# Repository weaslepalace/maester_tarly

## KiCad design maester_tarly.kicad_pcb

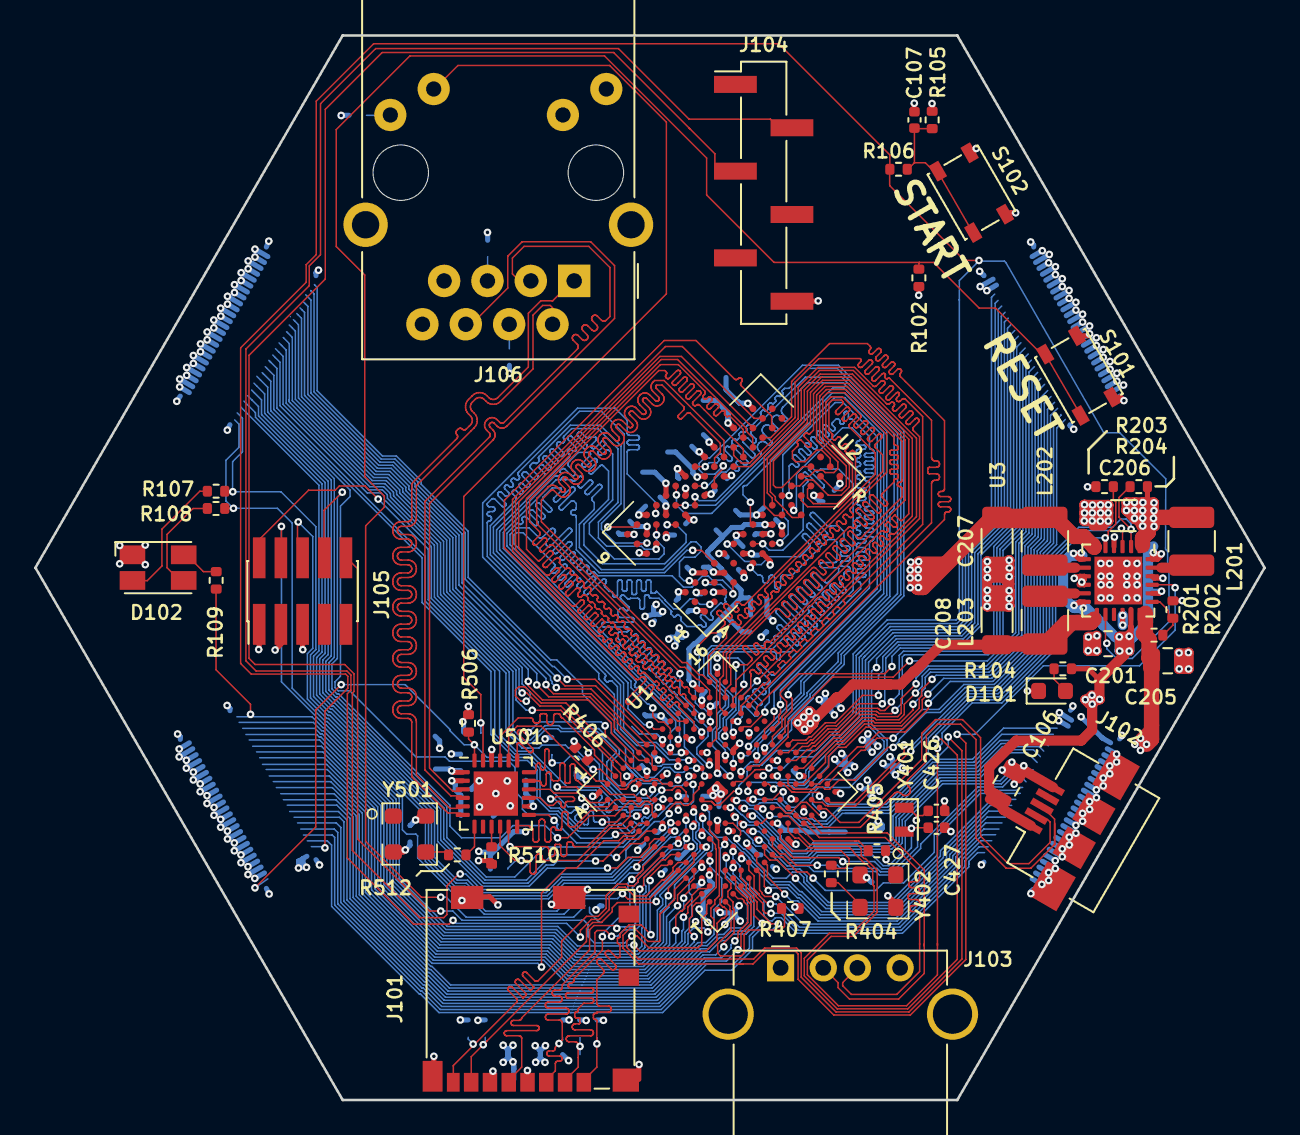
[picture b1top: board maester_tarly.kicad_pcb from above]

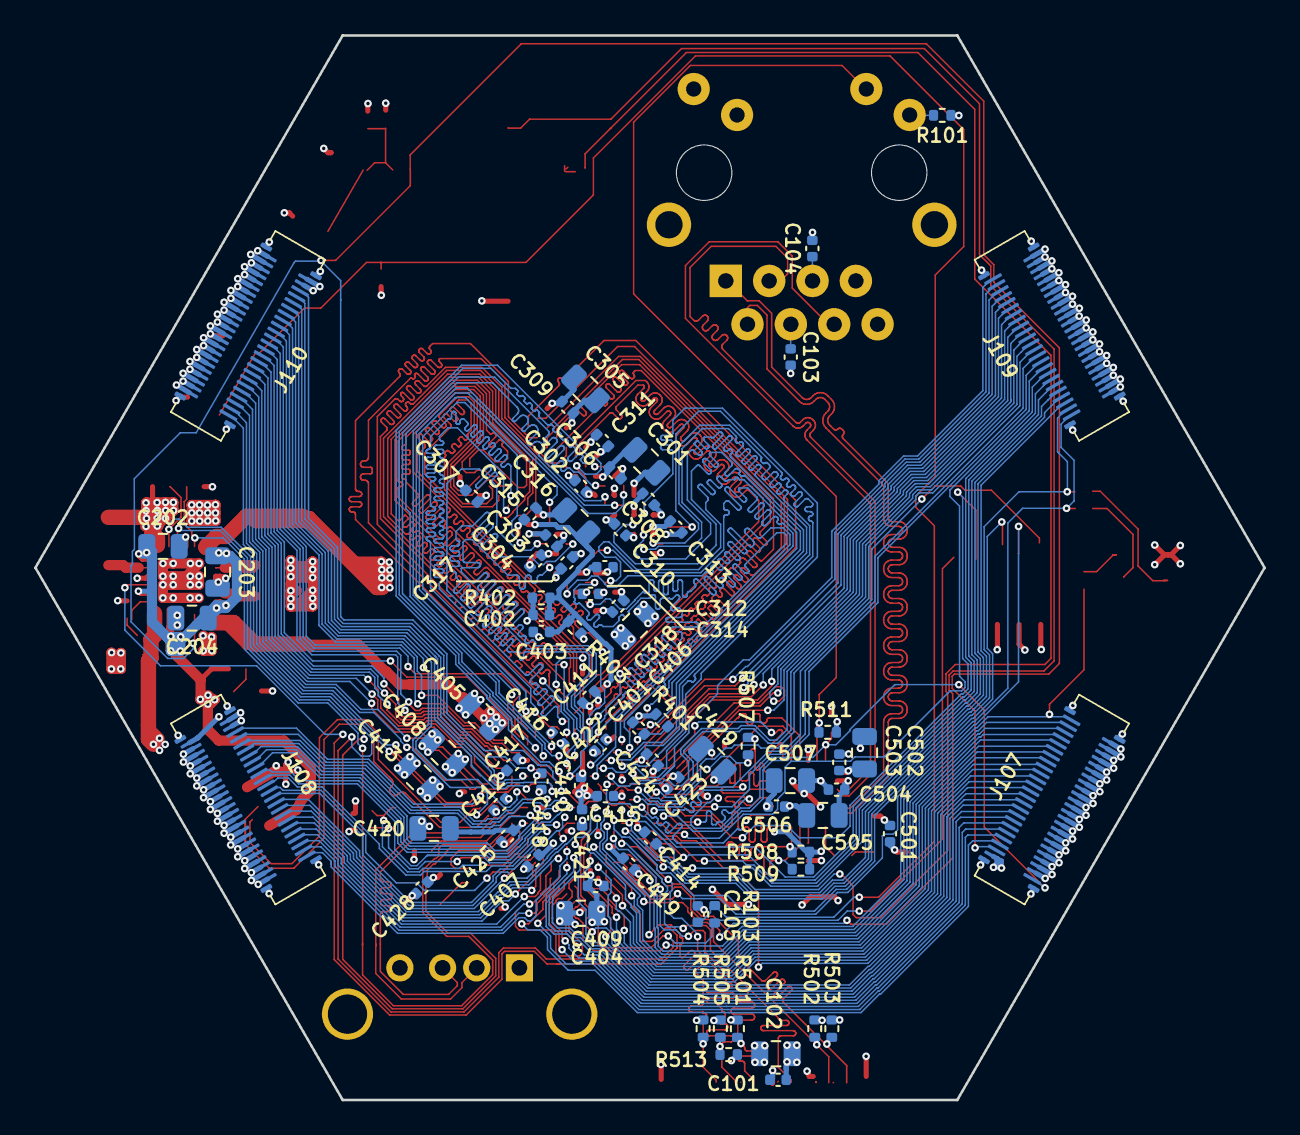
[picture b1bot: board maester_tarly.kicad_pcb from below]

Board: 4 copper layers, 72.0 x 62.4 mm, 126 parts (79 on the bottom side), 206 nets.

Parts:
C101, C103, C104, C105, C107, C302, C303, C304, C306, C307, C308, C309, C310, C311, C312, C313, C314, C315, C402, C403, C407, C409, C410, C411, C412, C414, C415, C416, C417, C418, C419, C421, C422, C423, C424, C425, C428, C501, C503, C504, C506: 100nF; C_0402_1005Metric
C102, C202, C203, C204, C205, C301, C305, C404, C405, C406, C408, C413, C420: 4.7uF; C_0805_2012Metric
C106: 10uF; C_0805_2012Metric
C201: 2.2uF; R_0805_2012Metric
C206, C207, C208: 22uF; R_1206_3216Metric
C316: 10nF; C_0805_2012Metric
C317, C318: 1nF; C_0402_1005Metric
C401: 22pF; C_0402_1005Metric
C426, C427: 20pF; C_0402_1005Metric
C429: 1uF; C_0805_2012Metric
C502, C505, C507: 2.2uF; C_0805_2012Metric
D101: Green; LED_0603_1608Metric
D102: ASMB-MTB0-0A3A2; LED_Avago_PLCC4_3.2x2.8mm_CW
J101: Micro_SD_Card_Det; microSD_HC_Molex_104031-0811
J102: USB_B_Micro; USB_Micro-B_Amphenol_10104110_Horizontal
J103: USB_A; USB_A_Stewart_SS-52100-001_Horizontal
J104: Conn_01x06; PinHeader_1x06_P2.54mm_Vertical_SMD_Pin1Left
J105: Conn_01x10; PinHeader_2x05_P1.27mm_Vertical_SMD
J106: RJ45_Amphenol_RJMG1BD3B8K1ANR
J107, J108, J109, J110: DF40GB(1.5)-48DS-0.4V; DF40GB(1.5)-48DS-0.4V(51)-CONNECTOR
L201, L202, L203: 2.2uH; L_1210_3225Metric
R101: 470R; R_0402_1005Metric
R102, R105, R203, R204, R407: 100k; R_0402_1005Metric
R103, R106: 100R; R_0402_1005Metric
R104, R107, R108, R109: 1k; R_0402_1005Metric
R201, R202: TBD; R_0402_1005Metric
R401: 20k; R_0402_1005Metric
R402, R403, R507: 4.7k; R_0402_1005Metric
R404, R510: 51R; R_0402_1005Metric
R405: 5.62k; R_0402_1005Metric
R406: 10R; R_0402_1005Metric
R501, R502, R503, R504, R505, R506, R508, R509, R511: 10k; R_0402_1005Metric
R512: 6.49k; R_0402_1005Metric
R513: 270k; R_0402_1005Metric
S101, S102: SW_Push; SW_SPST_PTS810
U1: SAM9X60; TFBGA228-SAM9X60
U2: W971GG6SB-18; WBGA84-DDR2-SDRAM
U3: MCP16501; QFN-24-1EP_4x4mm_P0.5mm_EP2.8x2.8mm
U501: KSZ8081RNA; QFN-24-1EP_4x4mm_P0.5mm_EP2.6x2.6mm
Y401: 32.768kHz; Crystal_SMD_2012-2Pin_2.0x1.2mm
Y402, Y501: DSC1001; VDFN4-3.2x2.5-DSC1001

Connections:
+1.8V: C207.1, C301.1, C302.1, C303.1, C304.1, C305.1, C306.1, C307.1, C308.1, C309.1, C310.1, C311.1, C312.1, C313.1, C314.1, C315.1, C317.1, C318.1, C402.1, C406.1, C411.1, C416.1, C422.1, L202.2, R402.1, U1.C10, U1.C13, U1.G14, U2.A1, U2.A9, U2.C1, U2.C3, U2.C7, U2.C9, U2.E1, U2.E9, U2.G1, U2.G3, U2.G7, U2.G9, U2.J1, U2.J9, U2.M9, U2.R1, U3.6
+1.15V: C208.1, C405.1, C410.1, C415.1, C421.1, L203.2, U1.F6, U1.F11, U1.L6, U3.13
+3V3: C101.1, C102.1, C206.1, C404.1, C407.1, C408.1, C409.1, C412.1, C413.1, C414.1, C417.1, C418.1, C419.1, C423.1, C424.1, C428.1, C501.1, C504.1, C505.1, C506.1, C507.1, D102.1, J101.4, J105.1, J108.1, J108.2, J108.4, L201.2, R101.1, R102.1, R105.1, R203.1, R204.2, R406.1, R501.1, R502.1, R503.1, R504.1, R505.1, R506.1, R507.1, R508.1, R509.1, R511.1, U1.C4, U1.C7, U1.G3, U1.K3, U1.K14, U1.L11, U1.N3, U1.P7, U1.P13, U3.1, U501.2, U501.14, Y402.4, Y501.4
+5V: C106.1, C201.1, C202.1, C203.1, C204.1, J102.1, J103.1, J110.2, J110.4, R104.1, U3.7, U3.12, U3.17, U3.20, U3.24
/CPU_CORE/CPU_DDR_CAS: U1.C12, U2.L7
/CPU_CORE/CPU_DDR_CKE: U1.F13, U2.K2
/CPU_CORE/CPU_DDR_CLK_N: U1.B14, U2.K8
/CPU_CORE/CPU_DDR_CLK_P: U1.A15, U2.J8
/CPU_CORE/CPU_DDR_CS: U1.E16, U2.L8
/CPU_CORE/CPU_DDR_HIGH_MASK: U1.C8, U2.B3
/CPU_CORE/CPU_DDR_HIGH_STROBE_N: U1.E9, U2.A8
/CPU_CORE/CPU_DDR_HIGH_STROBE_P: U1.D9, U2.B7
/CPU_CORE/CPU_DDR_LOW_MASK: U1.G11, U2.F3
/CPU_CORE/CPU_DDR_LOW_STROBE_N: U1.H13, U2.E8
/CPU_CORE/CPU_DDR_LOW_STROBE_P: U1.H12, U2.F7
/CPU_CORE/CPU_DDR_RAS: U1.E15, U2.K7
/CPU_CORE/CPU_DDR_VREF: C316.1, C402.2, C403.1, R402.2, R403.1, U1.A14, U2.J2
/CPU_CORE/CPU_DDR_WE: U1.D16, U2.K3
/CPU_CORE/CPU_JTAG_TCK: J105.4, U1.R3
/CPU_CORE/CPU_JTAG_TDI: J105.8, U1.F3
/CPU_CORE/CPU_JTAG_TDO: J105.6, U1.H5
/CPU_CORE/CPU_JTAG_TMS: J105.2, U1.F5
/CPU_CORE/CPU_SHUTDOWN: U1.R11, U3.3
/CPU_CORE/CPU_USB_DEVICE_N: J103.2, U1.R12
/CPU_CORE/CPU_USB_DEVICE_P: J103.3, U1.T12
/CPU_CORE/CPU_USB_HOST_N: J102.2, U1.T14
/CPU_CORE/CPU_USB_HOST_P: J102.3, U1.T13
/CPU_CORE/CPU_WAKEUP: R203.2, U1.T11, U3.5
/CPU_CORE/addr0: U1.A13, U2.M8
/CPU_CORE/addr1: U1.D15, U2.M3
/CPU_CORE/addr2: U1.B12, U2.M7
/CPU_CORE/addr3: U1.E11, U2.N2
/CPU_CORE/addr4: U1.A12, U2.N8
/CPU_CORE/addr5: U1.B16, U2.N3
/CPU_CORE/addr6: U1.F16, U2.N7
/CPU_CORE/addr7: U1.D14, U2.P2
/CPU_CORE/addr8: U1.C11, U2.P8
/CPU_CORE/addr9: U1.E13, U2.P3
/CPU_CORE/addr10: U1.D12, U2.M2
/CPU_CORE/addr11: U1.B11, U2.P7
/CPU_CORE/addr12: U1.C15, U2.R2
/CPU_CORE/bank0: U1.E14, U2.L2
/CPU_CORE/bank1: U1.F14, U2.L3
/CPU_CORE/bank2: U1.C16, U2.L1
/CPU_CORE/data0: U1.J13, U2.G8
/CPU_CORE/data1: U1.H11, U2.G2
/CPU_CORE/data2: U1.J11, U2.H7
/CPU_CORE/data3: U1.H16, U2.H3
/CPU_CORE/data4: U1.H15, U2.H1
/CPU_CORE/data5: U1.J14, U2.H9
/CPU_CORE/data6: U1.H10, U2.F1
/CPU_CORE/data7: U1.J16, U2.F9
/CPU_CORE/data8: U1.A9, U2.C8
/CPU_CORE/data9: U1.F10, U2.C2
/CPU_CORE/data10: U1.B9, U2.D7
/CPU_CORE/data11: U1.C9, U2.D3
/CPU_CORE/data12: U1.G9, U2.D1
/CPU_CORE/data13: U1.F9, U2.D9
/CPU_CORE/data14: U1.D11, U2.B1
/CPU_CORE/data15: U1.D8, U2.B9
/CPU_IO/CPU_DBG_UART_RX: J104.3, U1.G8
/CPU_IO/CPU_DBG_UART_TX: J104.2, U1.L2
/CPU_IO/CPU_ETH_LED: J106.L2, R511.2, U501.23
/CPU_IO/CPU_ETH_RX_N: J106.R6, U501.3
/CPU_IO/CPU_ETH_RX_P: J106.R3, U501.4
/CPU_IO/CPU_ETH_TX_N: J106.R2, U501.5
/CPU_IO/CPU_ETH_TX_P: J106.R1, U501.6
/CPU_IO/CPU_MMC_CLK: J101.5, U1.J3
/CPU_IO/CPU_MMC_CMD: J101.3, R501.2, U1.K2
/CPU_IO/PHY_CLK: U1.E3, U501.16
/CPU_IO/PHY_IRQ: R507.2, U1.E6, U501.18
/CPU_IO/PHY_MDC: R508.2, U1.D2, U501.11
/CPU_IO/PHY_MDIO: R509.2, U1.E1, U501.10
/CPU_IO/PHY_RXD0: U1.F4, U501.13
/CPU_IO/PHY_RXD1: U1.C1, U501.12
/CPU_IO/PHY_RXDV: U1.D1, U501.15
/CPU_IO/PHY_RXER: U1.D3, U501.17
/CPU_IO/PHY_TXD0: U1.A2, U501.20
/CPU_IO/PHY_TXD1: U1.A3, U501.21
/CPU_IO/PHY_TXEN: U1.A5, U501.19
/a0: J107.34, U1.P2
/a1: J107.30, U1.M3
/a2: J107.32, U1.P1
/a3: J107.42, U1.L3
/a4: J107.36, U1.N1
/a5: J107.44, U1.L4
/a6: J107.38, U1.M2
/a7: J107.28, U1.K6
/a12: J109.2, R108.2, U1.L1
/a13: J107.40, U1.J6
/a14: J107.46, U1.K1
/a21: J109.24, U1.G6
/a22: J109.14, U1.G1
/a23: J107.48, R109.2, U1.J4
/a24: J109.28, U1.F8
/a25: J109.4, R107.2, U1.H1
/a26: J109.16, U1.F7
/a27: J109.10, U1.H2
/a28: J107.26, U1.F1
/a29: J109.6, U1.H3
/a30: J109.12, U1.G2
/a31: J109.8, U1.H4
/b11: J109.48, U1.D6
/b12: J109.22, U1.C2
/b13: J109.32, U1.A4
/b14: J109.18, U1.F2
/b15: J109.34, U1.B5
/b16: J109.30, U1.B3
/b17: J109.20, U1.B1
/b18: J109.26, U1.E4
/b19: J109.40, U1.C6
/b20: J109.38, U1.A6
/b21: J109.42, U1.A7
/b22: J109.44, U1.B7
/b23: J109.36, U1.B6
/b24: J109.46, U1.A8
/c0: J107.22, U1.M4
/c1: J107.14, U1.P4
/c2: J107.18, U1.N5
/c3: J107.16, U1.P5
/c4: J107.24, U1.L5
/c5: J107.10, U1.R4
/c6: J107.20, U1.M6
/c7: J107.12, U1.T3
/c8: J108.22, U1.N8
/c9: J107.8, U1.T4
/c10: J108.36, U1.P6
/c11: J108.48, U1.N6
/c12: J107.6, U1.R5
/c13: J108.30, U1.L7
/c14: J108.46, U1.T5
/c15: J108.34, U1.J7
/c16: J108.44, U1.R6
/c17: J108.18, U1.K8
/c18: J108.42, U1.T6
/c19: J108.28, U1.L8
/c20: J108.24, U1.P8
/c21: J108.20, U1.M8
/c22: J108.38, U1.R7
/c23: J108.10, U1.K9
/c24: J108.32, U1.R8
/c25: J108.14, U1.L9
/c26: J108.26, U1.T8
/c27: J108.16, U1.M9
/c28: J108.12, U1.N9
/c29: J108.8, U1.L10
/c30: J108.40, U1.T7
/c31: J108.6, U1.M13
/cpu_reset: J105.10, R103.1, R204.1, U1.R1, U3.2
/d0: J110.48, U1.R14
/d1: J110.46, U1.T15
/d2: J110.40, U1.P15
/d3: J110.36, U1.N14
/d4: J110.42, U1.R16
/d5: J110.16, U1.N11
/d6: J110.18, U1.K16
/d7: J110.28, U1.J12
/d8: J110.20, U1.K15
/d9: J110.6, U1.J10
/d10: J110.24, U1.L16
/d11: J110.10, U1.K11
/d12: J110.26, U1.L15
/d13: J110.22, U1.J15
/d14: J110.12, U1.L12
/d15: J110.30, U1.M16
/d16: J110.44, U1.M14
/d17: J110.34, U1.N16
/d18: J110.8, U1.L13
/d19: J110.38, U1.P16
/d20: J110.14, U1.M11
/d21: J110.32, U1.M15
/ldo_en: U1.M1, U3.21
/ldo_out: C205.1, J107.2, R201.1, U3.18
/mmcdat0: J101.7, R502.2, U1.H6
/mmcdat1: J101.8, R503.2, U1.J1
/mmcdat2: J101.1, R504.2, U1.J5
/mmcdat3: J101.2, R505.2, R513.1, U1.J2
/periph_reset: J107.1, R506.2, U1.E2, U501.24
/start_btn: J107.4, R106.1, U1.H7, U3.14
GND: C101.2, C102.2, C103.2, C104.2, C105.2, C106.2, C107.2, C201.2, C202.2, C203.2, C204.2, C205.2, C206.2, C207.2, C208.2, C301.2, C302.2, C303.2, C304.2, C305.2, C306.2, C307.2, C308.2, C309.2, C310.2, C311.2, C312.2, C313.2, C314.2, C315.2, C316.2, C317.2, C318.2, C401.2, C403.2, C404.2, C405.2, C406.2, C407.2, C408.2, C409.2, C410.2, C411.2, C412.2, C413.2, C414.2, C415.2, C416.2, C417.2, C418.2, C419.2, C420.2, C421.2, C422.2, C423.2, C424.2, C425.2, C426.2, C427.1, C428.2, C429.2, C501.2, C502.2, C503.2, C504.2, C505.2, C506.2, C507.2, D101.1, J101.6, J101.11, J102.5, J102.6, J103.4, J103.5, J104.6, J105.3, J105.5, J106.13, J106.R8, J107.3, J107.5, J107.7, J107.9, J107.11, J107.13, J107.15, J107.17, J107.19, J107.21, J107.23, J107.25, J107.27, J107.29, J107.31, J107.33, J107.35, J107.37, J107.39, J107.41, J107.43, J107.45, J107.47, J107.S, J108.3, J108.5, J108.7, J108.9, J108.11, J108.13, J108.15, J108.17, J108.19, J108.21, J108.23, J108.25, J108.27, J108.29, J108.31, J108.33, J108.35, J108.37, J108.39, J108.41, J108.43, J108.45, J108.47, J108.S, J109.1, J109.3, J109.5, J109.7, J109.9, J109.11, J109.13, J109.15, J109.17, J109.19, J109.21, J109.23, J109.25, J109.27, J109.29, J109.31, J109.33, J109.35, J109.37, J109.39, J109.41, J109.43, J109.45, J109.47, J109.S, J110.1, J110.3, J110.5, J110.7, J110.9, J110.11, J110.13, J110.15, J110.17, J110.19, J110.21, J110.23, J110.25, J110.27, J110.29, J110.31, J110.33, J110.35, J110.37, J110.39, J110.41, J110.43, J110.45, J110.47, J110.S, R202.2, R401.2, R403.2, R405.1, R407.2, R512.1, R513.2, S101.1, S102.1, U1.A1, U1.A16, U1.B4, U1.B13, U1.C5, U1.E7, U1.E10, U1.G5, U1.G12, U1.H8, U1.H9, U1.J8, U1.J9, U1.K5, U1.K12, U1.M7, U1.M10, U1.N2, U1.N15, U1.R13, U1.T1, U1.T10, U1.T16, U2.A3, U2.A7, U2.B2, U2.B8, U2.D2, U2.D8, U2.E3, U2.E7, U2.F2, U2.F8, U2.H2, U2.H8, U2.J3, U2.J7, U2.K9, U2.N1, U2.P9, U3.4, U3.9, U3.10, U3.16, U3.22, U3.25, U501.22, U501.25, Y402.2, Y501.2
unnamed: C103.1, J106.R4
unnamed: C104.1, J106.R5
unnamed: C105.1, R102.2, R103.2, S101.2
unnamed: C107.1, R105.2, R106.2, S102.2
unnamed: C401.1, R401.1, U1.B8
unnamed: C420.1, C425.1, U1.P10
unnamed: C426.1, U1.R9, Y401.1
unnamed: C427.2, U1.T9, Y401.2
unnamed: C429.1, R406.2, U1.D5
unnamed: C502.1, C503.1, U501.1
unnamed: D101.2, R104.2
unnamed: D102.2, R109.1
unnamed: D102.3, R108.1
unnamed: D102.4, R107.1
unnamed: J106.L1, R101.2
unnamed: L201.1, U3.23
unnamed: L202.1, U3.8
unnamed: L203.1, U3.11
unnamed: R201.2, R202.1, U3.19
unnamed: R404.1, U1.R10
unnamed: R404.2, Y402.3
unnamed: R405.2, U1.P11
unnamed: R407.1, U1.T2
unnamed: R510.1, U501.7
unnamed: R510.2, Y501.3
unnamed: R512.2, U501.9

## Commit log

2020-12-13 Routed DDR2 bus
2021-01-01 Escaped all traced from the CPU
2021-01-17 Placed all the parts. Some will have to move.
2021-01-17 Routed power supply traces and vias. Repositioned mezzanine connectors.
2021-01-19 Wired up J107 and J109
2021-01-24 27 Unrouted traces remaiin.
2021-01-24 Cleaned silkscreen, routed all traces, USB-A and SD need rerouting, need to redo ram wiggles
2021-01-31 Redid all the wiggle-wiggles
2021-01-31 Clean DRC
